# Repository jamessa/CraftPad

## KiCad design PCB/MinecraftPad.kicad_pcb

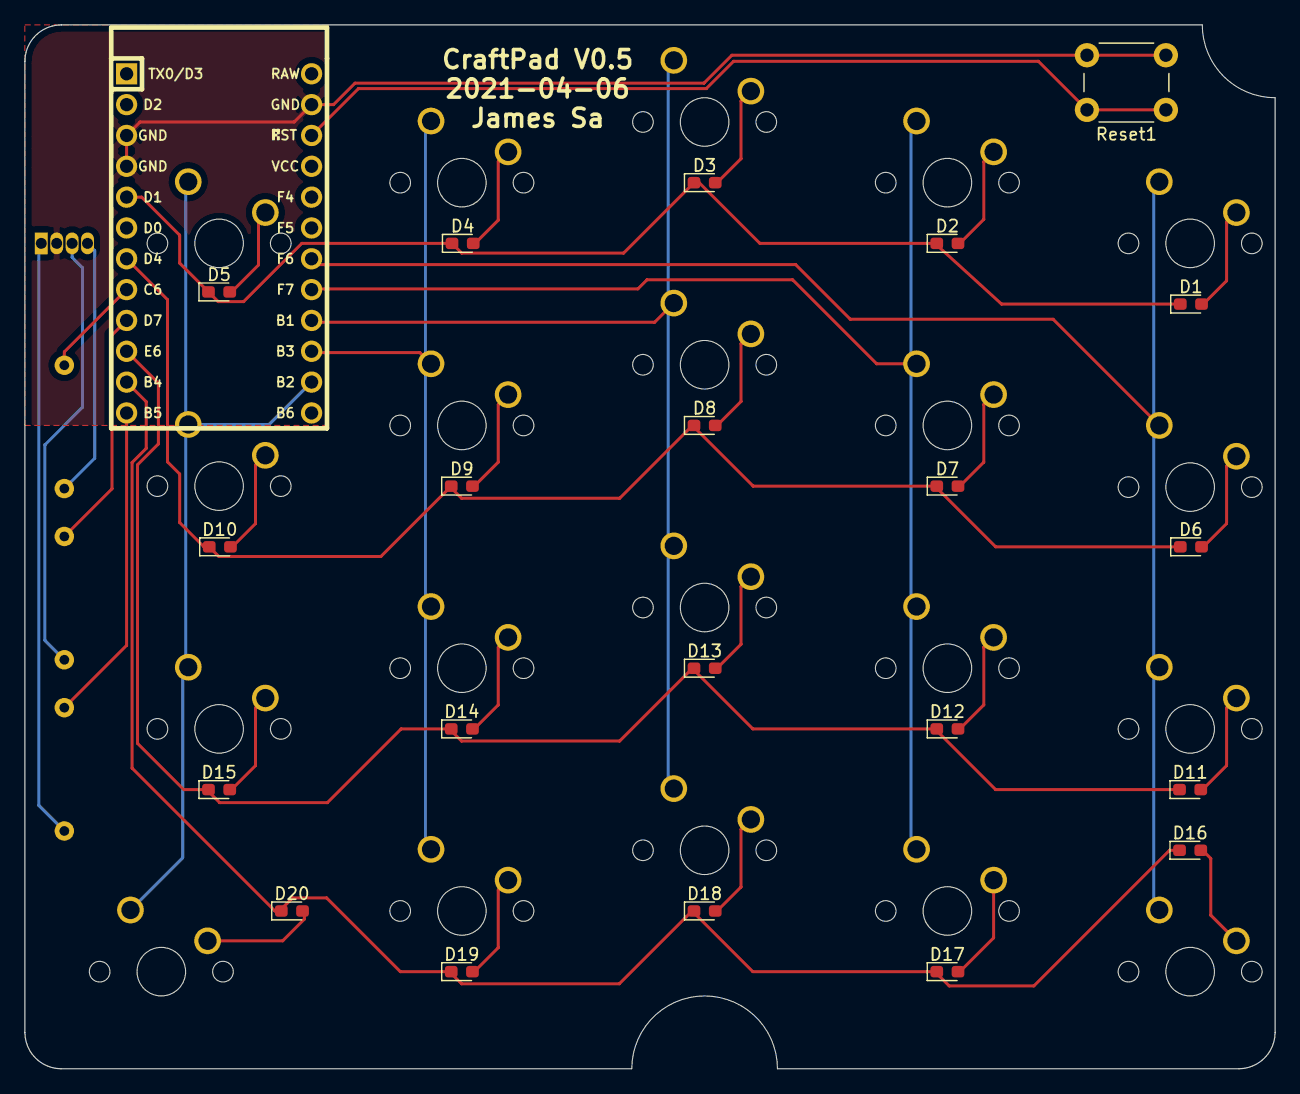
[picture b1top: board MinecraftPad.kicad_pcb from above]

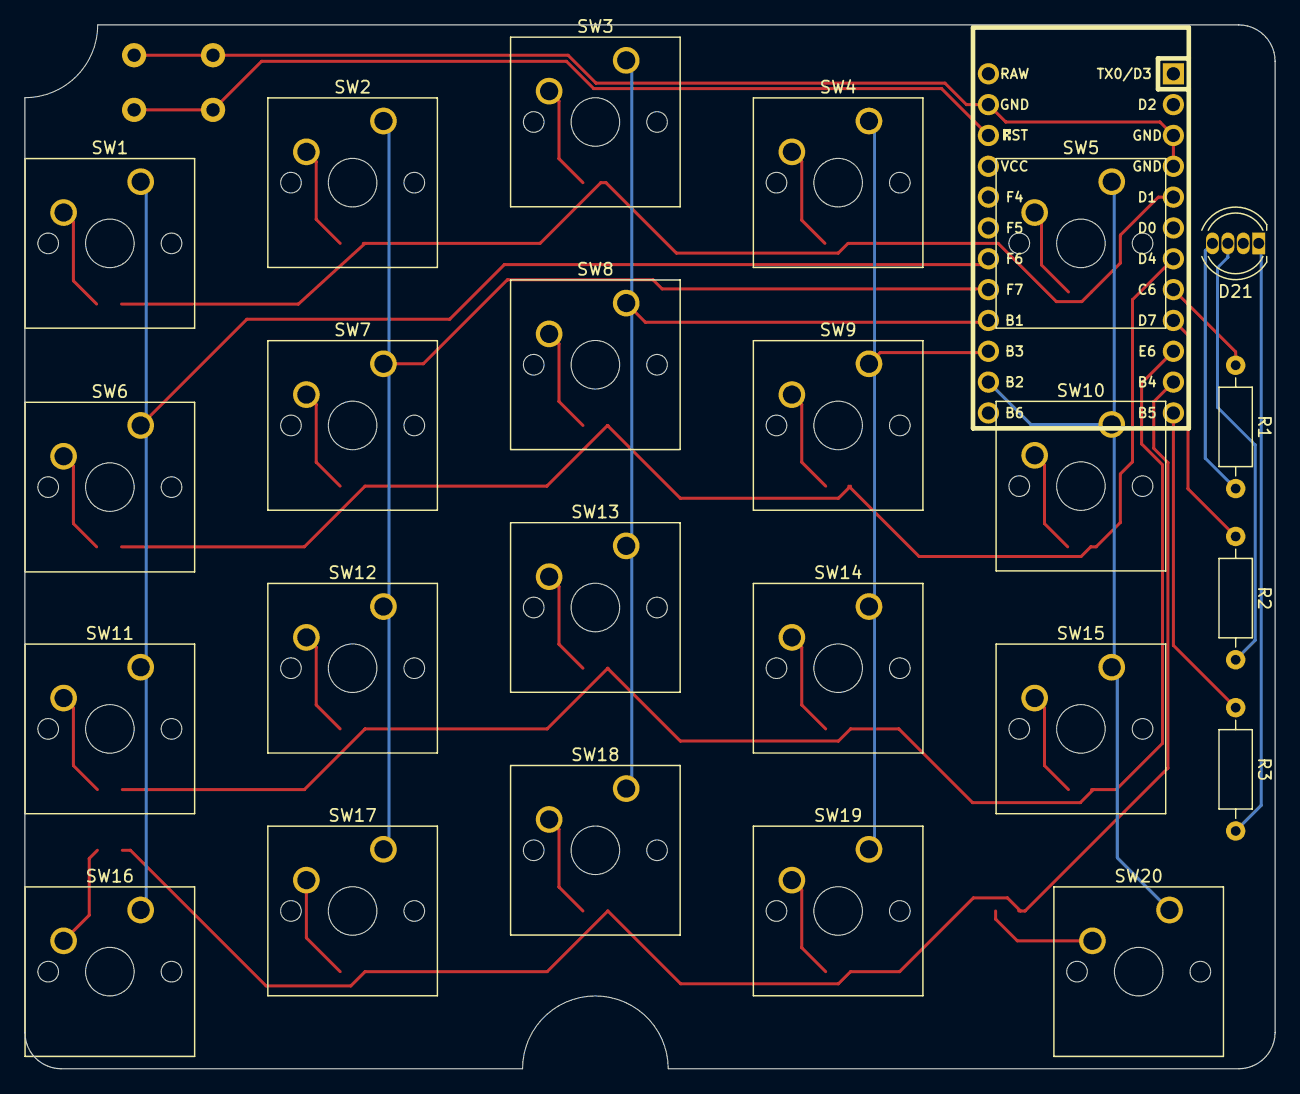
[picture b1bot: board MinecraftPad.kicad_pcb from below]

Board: 2 copper layers, 103.0 x 86.0 mm, 46 parts (24 on the bottom side), 37 nets.

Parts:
B1: PRO MICRO; ArduinoProMicro
D1, D2, D3, D4, D5, D6, D7, D8, D9, D10, D11, D12, D13, D14, D15, D16, D17, D18, D19, D20: D; D_0603_1608Metric_Pad1.05x0.95mm_HandSolder
D21: LED_RCGB; LED_D5.0mm-4_RGB
R1, R2, R3: 220Ω; R_Axial_DIN0207_L6.3mm_D2.5mm_P10.16mm_Horizontal
Reset1: SW_Push; SW_PUSH_6mm
SW1, SW2, SW3, SW4, SW5, SW6, SW7, SW8, SW9, SW10, SW11, SW12, SW13, SW14, SW15, SW16, SW17, SW18, SW19: SW_Push; SW_Cherry_MX_1.00u_PCB
SW20: SW_Push; SW_Cherry_MX_1.50u_PCB

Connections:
Blue: B1.8, R1.1
Col1: B1.18, SW1.1, SW6.1, SW11.1, SW16.1
Col2: B1.17, SW2.1, SW7.1, SW12.1, SW17.1
Col3: B1.16, SW3.1, SW8.1, SW13.1, SW18.1
Col4: B1.15, SW4.1, SW9.1, SW14.1, SW19.1
Col5: B1.14, SW5.1, SW10.1, SW15.1, SW20.1
GND: B1.3, B1.4, B1.23, D21.2, Reset1.2
Green: B1.9, R2.1
unnamed: B1.22, Reset1.1
unnamed: D1.2, SW1.2
unnamed: D2.2, SW2.2
unnamed: D3.2, SW3.2
unnamed: D4.2, SW4.2
unnamed: D5.2, SW5.2
unnamed: D6.2, SW6.2
unnamed: D7.2, SW7.2
unnamed: D8.2, SW8.2
unnamed: D9.2, SW9.2
unnamed: D10.2, SW10.2
unnamed: D11.2, SW11.2
unnamed: D12.2, SW12.2
unnamed: D13.2, SW13.2
unnamed: D14.2, SW14.2
unnamed: D15.2, SW15.2
unnamed: D16.2, SW16.2
unnamed: D17.2, SW17.2
unnamed: D18.2, SW18.2
unnamed: D19.2, SW19.2
unnamed: D20.2, SW20.2
unnamed: D21.1, R3.2
unnamed: D21.3, R2.2
unnamed: D21.4, R1.2
Red: B1.12, R3.1
Row1: B1.5, D1.1, D2.1, D3.1, D4.1, D5.1
Row2: B1.7, D6.1, D7.1, D8.1, D9.1, D10.1
Row3: B1.10, D11.1, D12.1, D13.1, D14.1, D15.1
Row4: B1.11, D16.1, D17.1, D18.1, D19.1, D20.1

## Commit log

2021-04-01 init
2021-04-01 improvements
2021-04-02 v0.2
2021-04-05 v0.4
2021-04-05 update silkscreen
2021-04-05 RGBA
2021-04-06 v0.5
2021-04-06 tidy up
2021-04-06 rename
2021-07-26 notes
